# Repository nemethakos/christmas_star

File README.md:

# Christmas Star

Christmas Star is a Christmas ornament to be hanged onto a Christmas tree. 

It runs on a single AA Battery (Lithium, NiMh or Alkaline), has 31 APA102-2020 RGB LEDs driven by an ATMEGA 328P running on Arduino core. 
Gesture control by Avago APDS-9960 Gesture and Light sensor (sleep/wake up, next/previous effect).

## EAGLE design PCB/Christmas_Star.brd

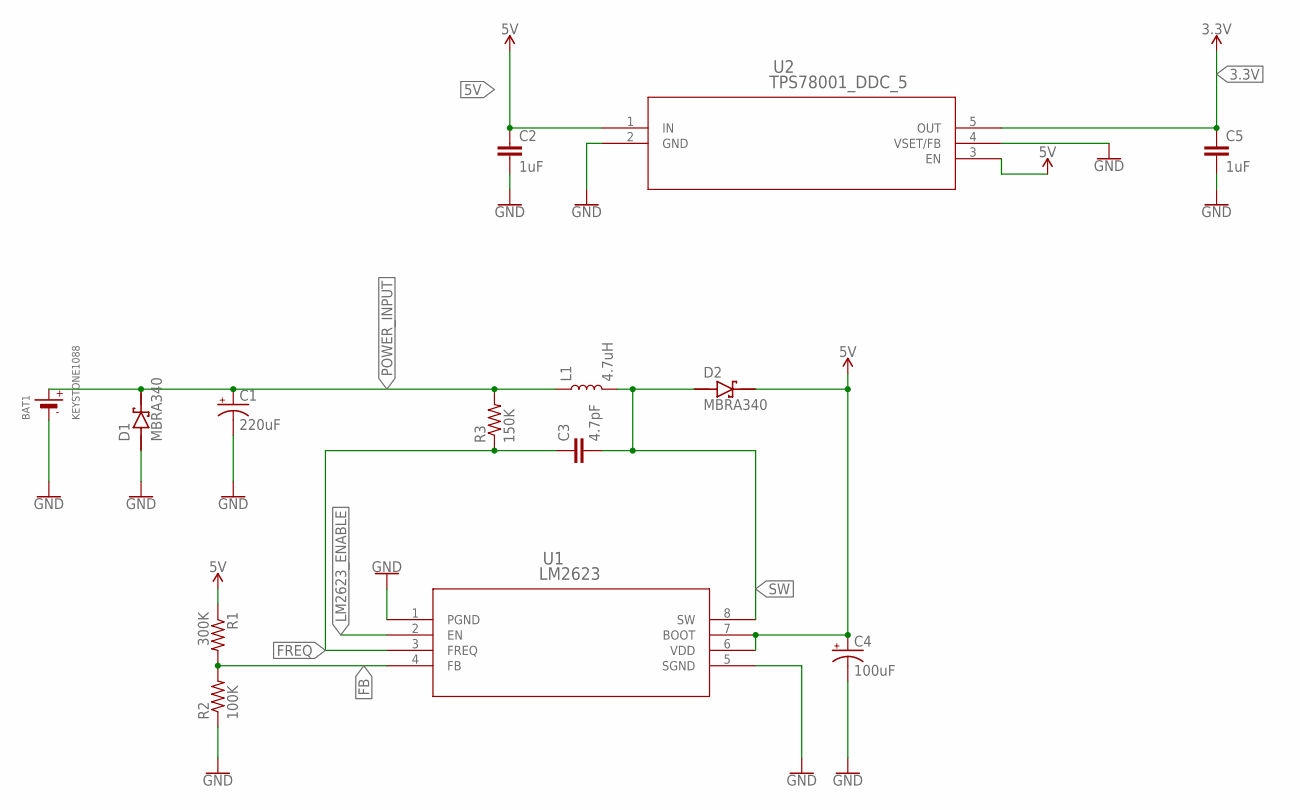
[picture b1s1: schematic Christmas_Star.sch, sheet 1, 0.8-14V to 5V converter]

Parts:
BAT1: KEYSTONE1088
C1: 220uF; EIA3528-KIT
C2, C5: 1uF; 0603-CAP
C3: 4.7pF; 0603-CAP
C4: 100uF; EIA3216-KIT
D1, D2: MBRA340; DIOM4427X270N
L1: 4.7uH; LTF5022
R1: 300K; 0603-RES
R2: 100K; 0603-RES
R3: 150K; 0603-RES
U1: LM2623; MUA08A
U2: TPS78001_DDC_5; DDC5

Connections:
3.3V: C5.1, U2.5 (OUT); also elsewhere on the board
5V: C2.1, C4.A (+), D2.C, R1.1, U1.6 (VDD), U1.7 (BOOT), U2.1 (IN), U2.3 (EN); also elsewhere on the board
FB: R1.2, R2.2, U1.4 (FB)
FREQ: C3.1, R3.1, U1.3 (FREQ)
GND: BAT1.-, C1.C (-), C2.2, C4.C (-), C5.2, D1.A, R2.1, U1.1 (PGND), U1.5 (SGND), U2.2 (GND), U2.4 (VSET/FB); also elsewhere on the board
LM2623_ENABLE: U1.2 (EN); also elsewhere on the board
POWER_INPUT: BAT1.+, C1.A (+), D1.C, L1.P$1 (1), R3.2; also elsewhere on the board
SW: C3.2, D2.A, L1.P$2 (2), U1.8 (SW)

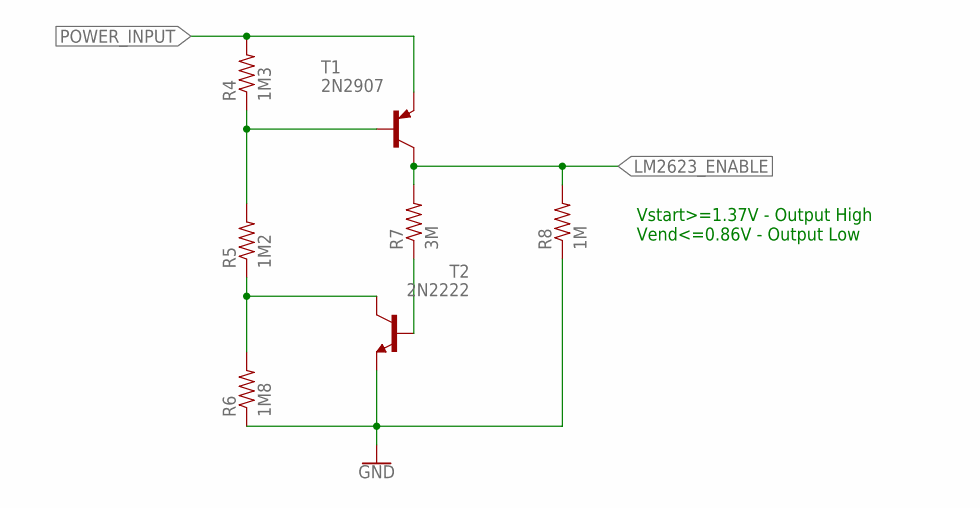
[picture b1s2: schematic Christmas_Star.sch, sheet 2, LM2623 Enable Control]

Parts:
R4: 1M3; 0603-RES
R5: 1M2; 0603-RES
R6: 1M8; 0603-RES
R7: 3M; 0603-RES
R8: 1M; 0603-RES
T1: 2N2907; SOT23-BEC
T2: 2N2222; SOT23-BEC

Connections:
GND: R6.1, R8.1, T2.E; also elsewhere on the board
LM2623_ENABLE: R7.2, R8.2, T1.C; also elsewhere on the board
unnamed: R4.1, R5.2, T1.B
unnamed: R5.1, R6.2, T2.C
unnamed: R7.1, T2.B
POWER_INPUT: R4.2, T1.E; also elsewhere on the board

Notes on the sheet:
Vstart>=1.37V - Output High Vend<=0.86V - Output Low

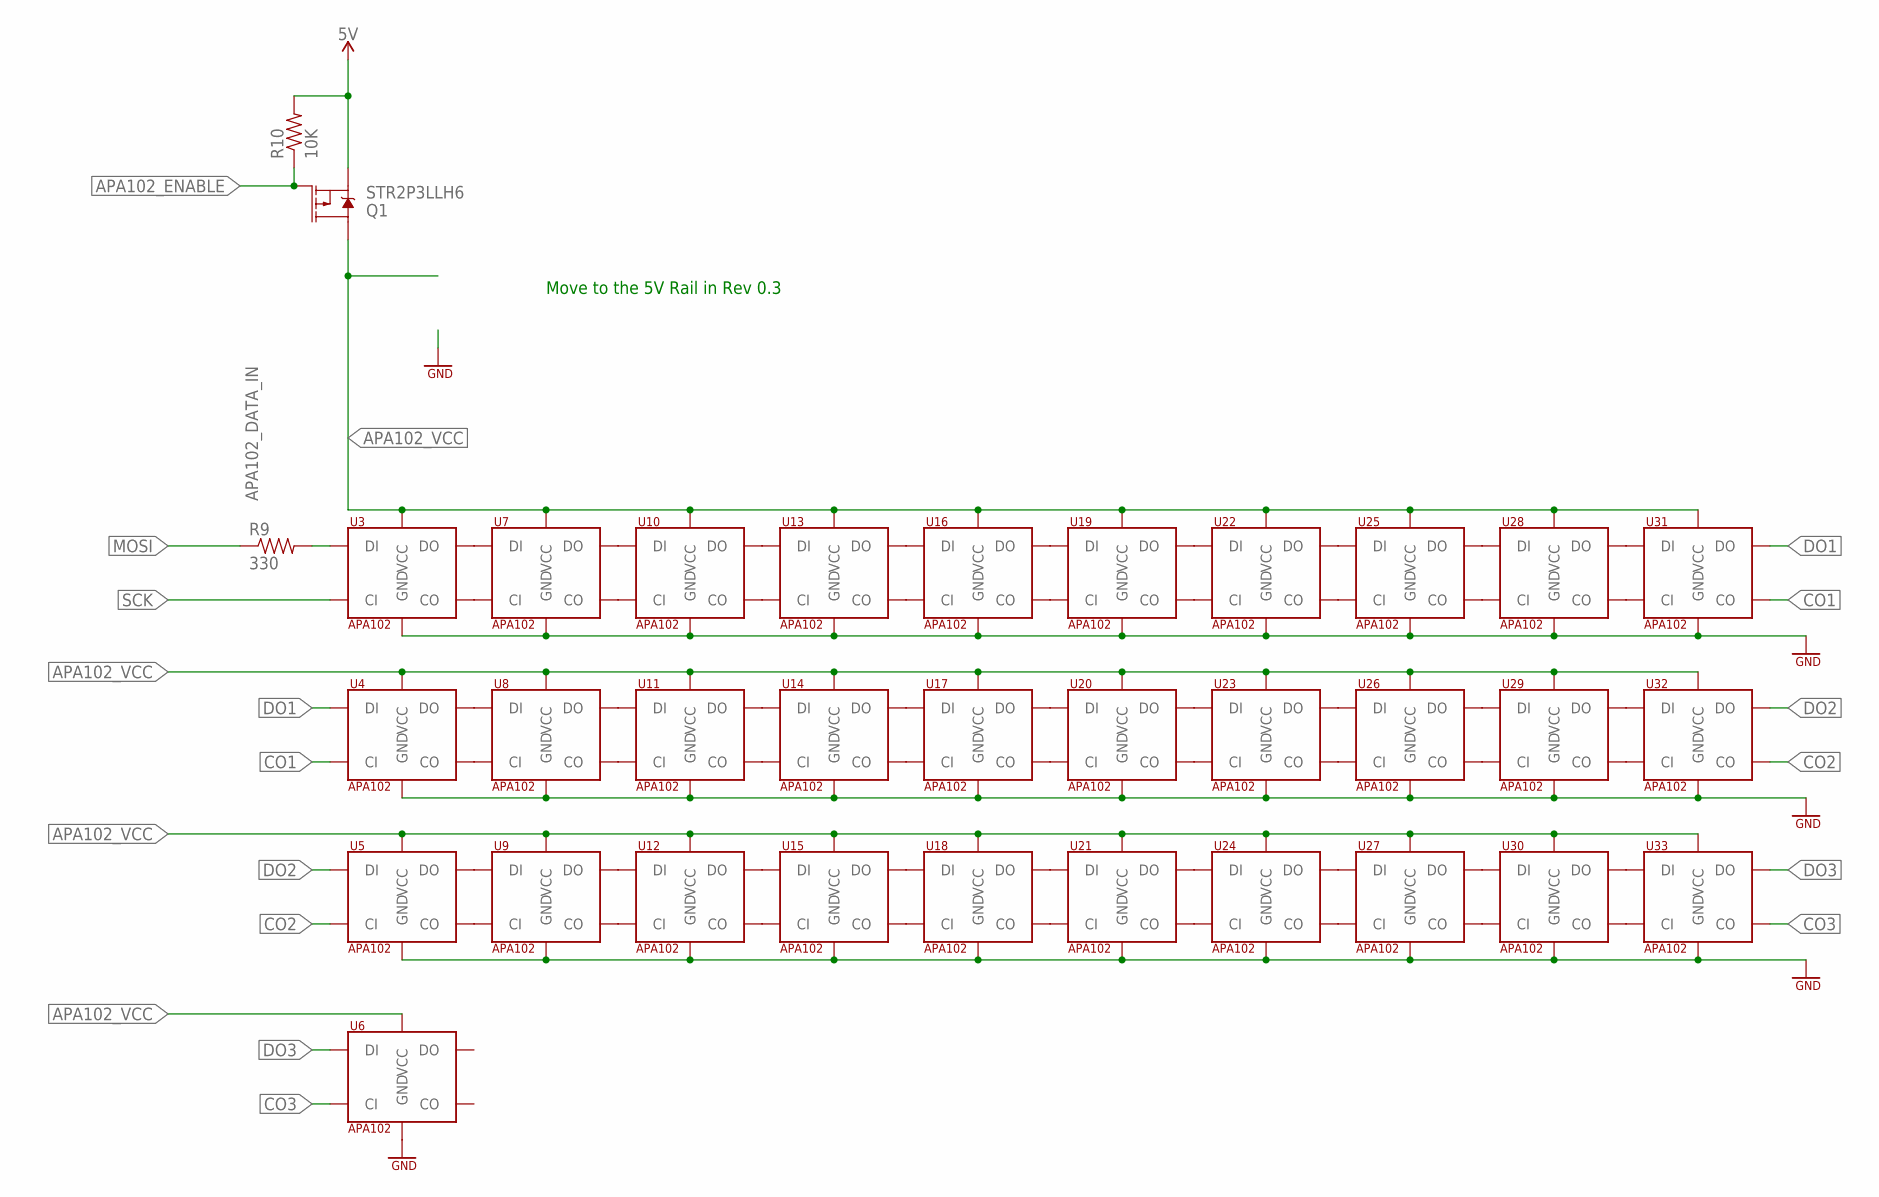
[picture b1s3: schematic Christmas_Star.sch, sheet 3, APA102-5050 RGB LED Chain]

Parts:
Q1: STR2P3LLH6; SOT23-3
R9: 330; 0603-RES
R10: 10K; 0603-RES
U3, U4, U5, U6, U7, U8, U9, U10, U11, U12, U13, U14, U15, U16, U17, U18, U19, U20, U21, U22, U23, U24, U25, U26, U27, U28, U29, U30, U31, U32, U33: APA102; APA102_2020

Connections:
5V: Q1.2 (S), R10.2; also elsewhere on the board
APA102_DATA_IN: R9.2, U3.D_IN (DI)
APA102_ENABLE: Q1.1 (G), R10.1; also elsewhere on the board
APA102_VCC: Q1.3 (D), U3.VCC, U4.VCC, U5.VCC, U6.VCC, U7.VCC, U8.VCC, U9.VCC, U10.VCC, U11.VCC, U12.VCC, U13.VCC, U14.VCC, U15.VCC, U16.VCC, U17.VCC, U18.VCC, U19.VCC, U20.VCC, U21.VCC, U22.VCC, U23.VCC, U24.VCC, U25.VCC, U26.VCC, U27.VCC, U28.VCC, U29.VCC, U30.VCC, U31.VCC, U32.VCC, U33.VCC
CO1: U4.C_IN (CI), U31.CL_OUT (CO)
CO2: U5.C_IN (CI), U32.CL_OUT (CO)
CO3: U6.C_IN (CI), U33.CL_OUT (CO)
DO1: U4.D_IN (DI), U31.D_OUT (DO)
DO2: U5.D_IN (DI), U32.D_OUT (DO)
DO3: U6.D_IN (DI), U33.D_OUT (DO)
GND: U3.GND, U4.GND, U5.GND, U6.GND, U7.GND, U8.GND, U9.GND, U10.GND, U11.GND, U12.GND, U13.GND, U14.GND, U15.GND, U16.GND, U17.GND, U18.GND, U19.GND, U20.GND, U21.GND, U22.GND, U23.GND, U24.GND, U25.GND, U26.GND, U27.GND, U28.GND, U29.GND, U30.GND, U31.GND, U32.GND, U33.GND; also elsewhere on the board
MOSI: R9.1; also elsewhere on the board
unnamed: U3.D_OUT (DO), U7.D_IN (DI)
unnamed: U3.CL_OUT (CO), U7.C_IN (CI)
unnamed: U7.D_OUT (DO), U10.D_IN (DI)
unnamed: U7.CL_OUT (CO), U10.C_IN (CI)
unnamed: U10.D_OUT (DO), U13.D_IN (DI)
unnamed: U10.CL_OUT (CO), U13.C_IN (CI)
unnamed: U13.D_OUT (DO), U16.D_IN (DI)
unnamed: U13.CL_OUT (CO), U16.C_IN (CI)
unnamed: U16.D_OUT (DO), U19.D_IN (DI)
unnamed: U16.CL_OUT (CO), U19.C_IN (CI)
unnamed: U19.D_OUT (DO), U22.D_IN (DI)
unnamed: U19.CL_OUT (CO), U22.C_IN (CI)
unnamed: U22.D_OUT (DO), U25.D_IN (DI)
unnamed: U22.CL_OUT (CO), U25.C_IN (CI)
unnamed: U25.D_OUT (DO), U28.D_IN (DI)
unnamed: U25.CL_OUT (CO), U28.C_IN (CI)
unnamed: U28.D_OUT (DO), U31.D_IN (DI)
unnamed: U28.CL_OUT (CO), U31.C_IN (CI)
unnamed: U4.D_OUT (DO), U8.D_IN (DI)
unnamed: U4.CL_OUT (CO), U8.C_IN (CI)
unnamed: U8.D_OUT (DO), U11.D_IN (DI)
unnamed: U8.CL_OUT (CO), U11.C_IN (CI)
unnamed: U11.D_OUT (DO), U14.D_IN (DI)
unnamed: U11.CL_OUT (CO), U14.C_IN (CI)
unnamed: U14.D_OUT (DO), U17.D_IN (DI)
unnamed: U14.CL_OUT (CO), U17.C_IN (CI)
unnamed: U17.D_OUT (DO), U20.D_IN (DI)
unnamed: U17.CL_OUT (CO), U20.C_IN (CI)
unnamed: U20.D_OUT (DO), U23.D_IN (DI)
unnamed: U20.CL_OUT (CO), U23.C_IN (CI)
unnamed: U23.D_OUT (DO), U26.D_IN (DI)
unnamed: U23.CL_OUT (CO), U26.C_IN (CI)
unnamed: U26.D_OUT (DO), U29.D_IN (DI)
unnamed: U26.CL_OUT (CO), U29.C_IN (CI)
unnamed: U29.D_OUT (DO), U32.D_IN (DI)
unnamed: U29.CL_OUT (CO), U32.C_IN (CI)
unnamed: U5.D_OUT (DO), U9.D_IN (DI)
unnamed: U5.CL_OUT (CO), U9.C_IN (CI)
unnamed: U9.D_OUT (DO), U12.D_IN (DI)
unnamed: U9.CL_OUT (CO), U12.C_IN (CI)
unnamed: U12.D_OUT (DO), U15.D_IN (DI)
unnamed: U12.CL_OUT (CO), U15.C_IN (CI)
unnamed: U15.D_OUT (DO), U18.D_IN (DI)
unnamed: U15.CL_OUT (CO), U18.C_IN (CI)
unnamed: U18.D_OUT (DO), U21.D_IN (DI)
unnamed: U18.CL_OUT (CO), U21.C_IN (CI)
unnamed: U21.D_OUT (DO), U24.D_IN (DI)
unnamed: U21.CL_OUT (CO), U24.C_IN (CI)
unnamed: U24.D_OUT (DO), U27.D_IN (DI)
unnamed: U24.CL_OUT (CO), U27.C_IN (CI)
unnamed: U27.D_OUT (DO), U30.D_IN (DI)
unnamed: U27.CL_OUT (CO), U30.C_IN (CI)
unnamed: U30.D_OUT (DO), U33.D_IN (DI)
unnamed: U30.CL_OUT (CO), U33.C_IN (CI)
SCK: U3.C_IN (CI); also elsewhere on the board

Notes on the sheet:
Move to the 5V Rail in Rev 0.3

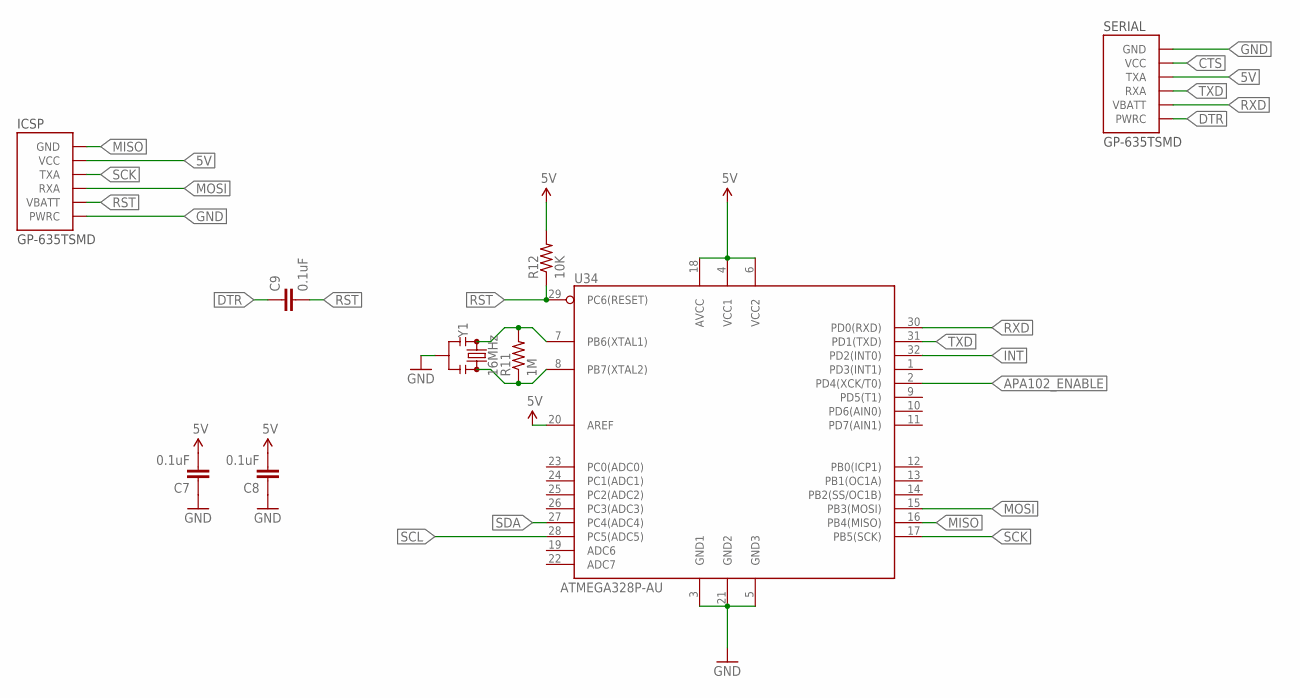
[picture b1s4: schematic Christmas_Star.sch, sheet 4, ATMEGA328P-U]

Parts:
C7, C8, C9: 0.1uF; 0603-CAP
ICSP: GP-635TSMD; GP-635T
R11: 1M; 0603-RES
R12: 10K; 0603-RES
SERIAL: GP-635TSMD; GP-635T
U34: ATMEGA328P-AU; TQFP32
Y1: 16MHz; RESONATOR-SMD-3.2X1.3

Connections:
5V: C7.2, C8.2, ICSP.2 (VCC), R12.2, SERIAL.3 (TXA), U34.4 (VCC1), U34.6 (VCC2), U34.18 (AVCC), U34.20 (AREF); also elsewhere on the board
APA102_ENABLE: U34.2 (PD4(XCK/T0)); also elsewhere on the board
CTS: SERIAL.2 (VCC)
DTR: C9.1, SERIAL.6 (PWRC)
GND: C7.1, C8.1, ICSP.6 (PWRC), SERIAL.1 (GND), U34.3 (GND1), U34.5 (GND3), U34.21 (GND2), Y1.2; also elsewhere on the board
INT: U34.32 (PD2(INT0)); also elsewhere on the board
MISO: ICSP.1 (GND), U34.16 (PB4(MISO))
MOSI: ICSP.4 (RXA), U34.15 (PB3(MOSI)); also elsewhere on the board
unnamed: R11.2, U34.7 (PB6(XTAL1)), Y1.1
unnamed: R11.1, U34.8 (PB7(XTAL2)), Y1.3
RST: C9.2, ICSP.5 (VBATT), R12.1, U34.29 (PC6(RESET))
RXD: SERIAL.5 (VBATT), U34.30 (PD0(RXD))
SCK: ICSP.3 (TXA), U34.17 (PB5(SCK)); also elsewhere on the board
SCL: U34.28 (PC5(ADC5)); also elsewhere on the board
SDA: U34.27 (PC4(ADC4)); also elsewhere on the board
TXD: SERIAL.4 (RXA), U34.31 (PD1(TXD))

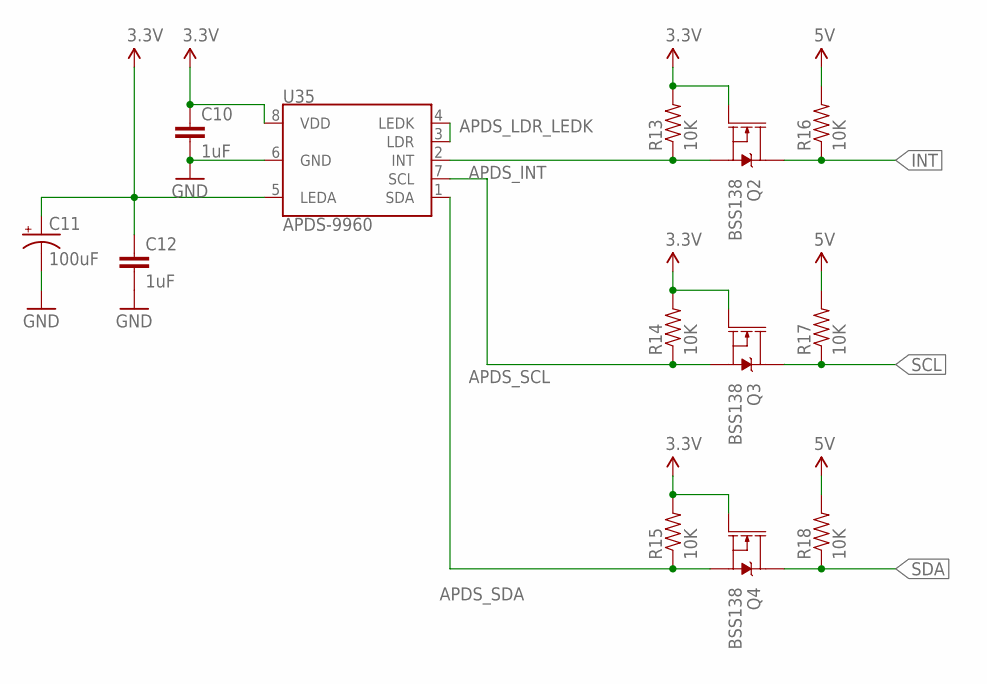
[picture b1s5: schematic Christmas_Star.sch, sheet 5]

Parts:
C10, C12: 1uF; 0603-CAP
C11: 100uF; EIA3216-KIT
Q2, Q3, Q4: BSS138; SOT23-3
R13, R14, R15, R16, R17, R18: 10K; 0603-RES
U35: APDS-9960

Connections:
3.3V: C10.1, C11.A (+), C12.1, Q2.1 (G), Q3.1 (G), Q4.1 (G), R13.2, R14.2, R15.2, U35.5 (LEDA), U35.8 (VDD); also elsewhere on the board
5V: R16.2, R17.2, R18.2; also elsewhere on the board
APDS_INT: Q2.2 (S), R13.1, U35.2 (INT)
APDS_LDR_LEDK: U35.3 (LDR), U35.4 (LEDK)
APDS_SCL: Q3.2 (S), R14.1, U35.7 (SCL)
APDS_SDA: Q4.2 (S), R15.1, U35.1 (SDA)
GND: C10.2, C11.C (-), C12.2, U35.6 (GND); also elsewhere on the board
INT: Q2.3 (D), R16.1; also elsewhere on the board
SCL: Q3.3 (D), R17.1; also elsewhere on the board
SDA: Q4.3 (D), R18.1; also elsewhere on the board

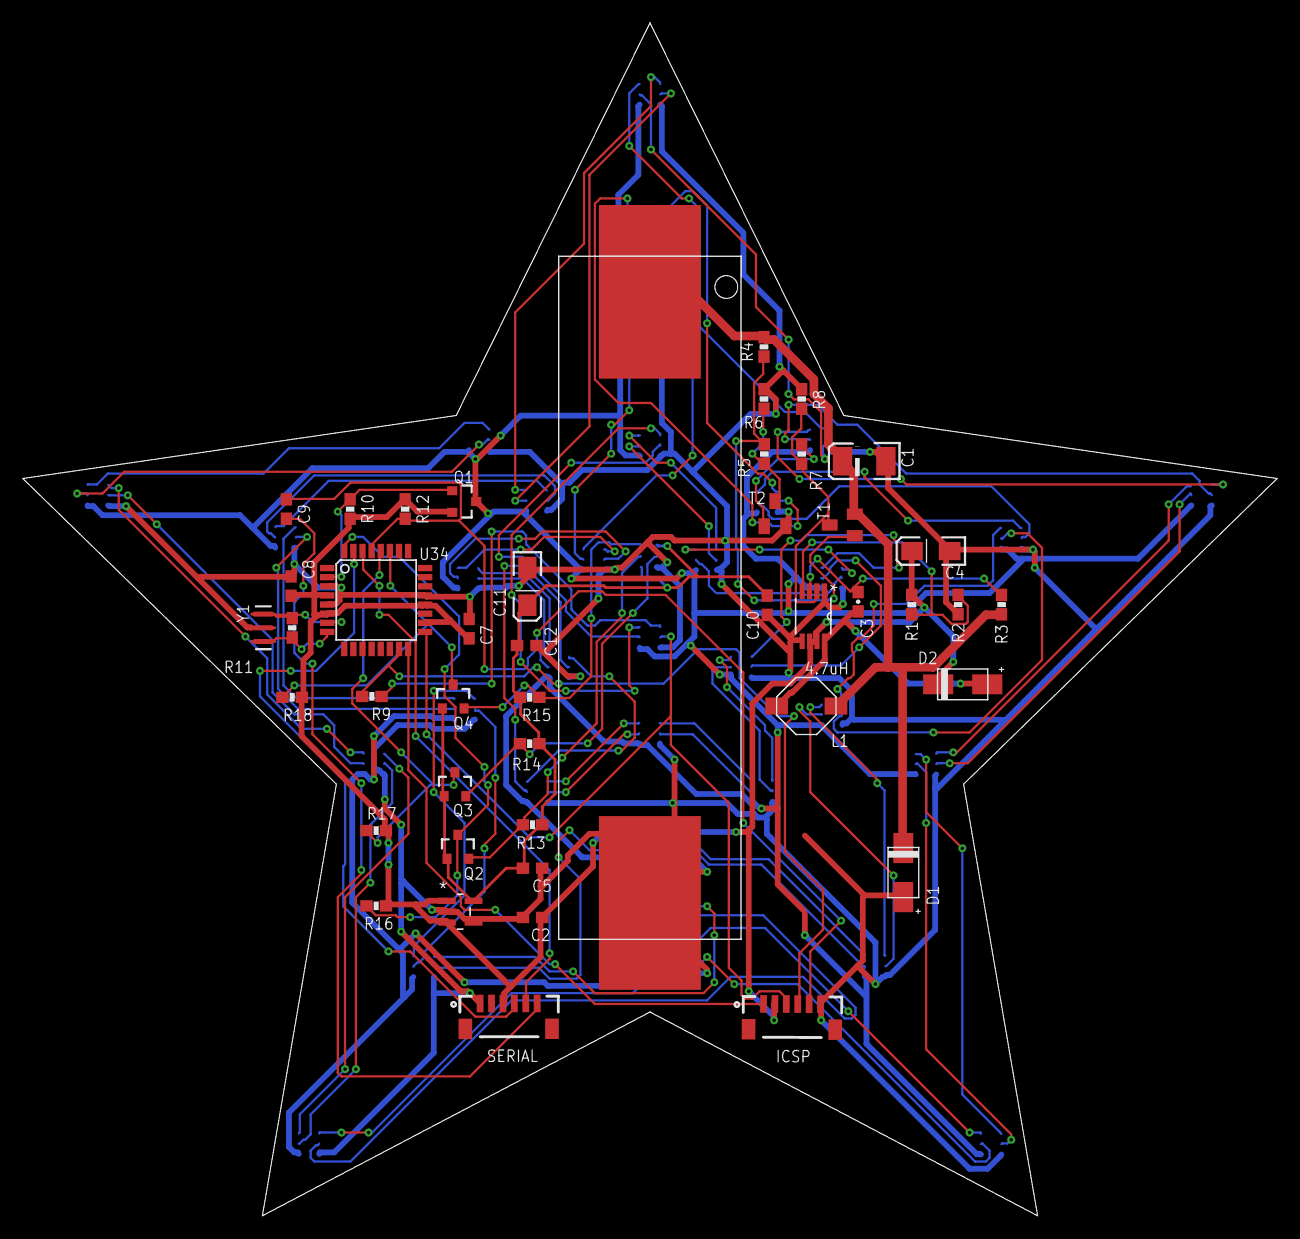
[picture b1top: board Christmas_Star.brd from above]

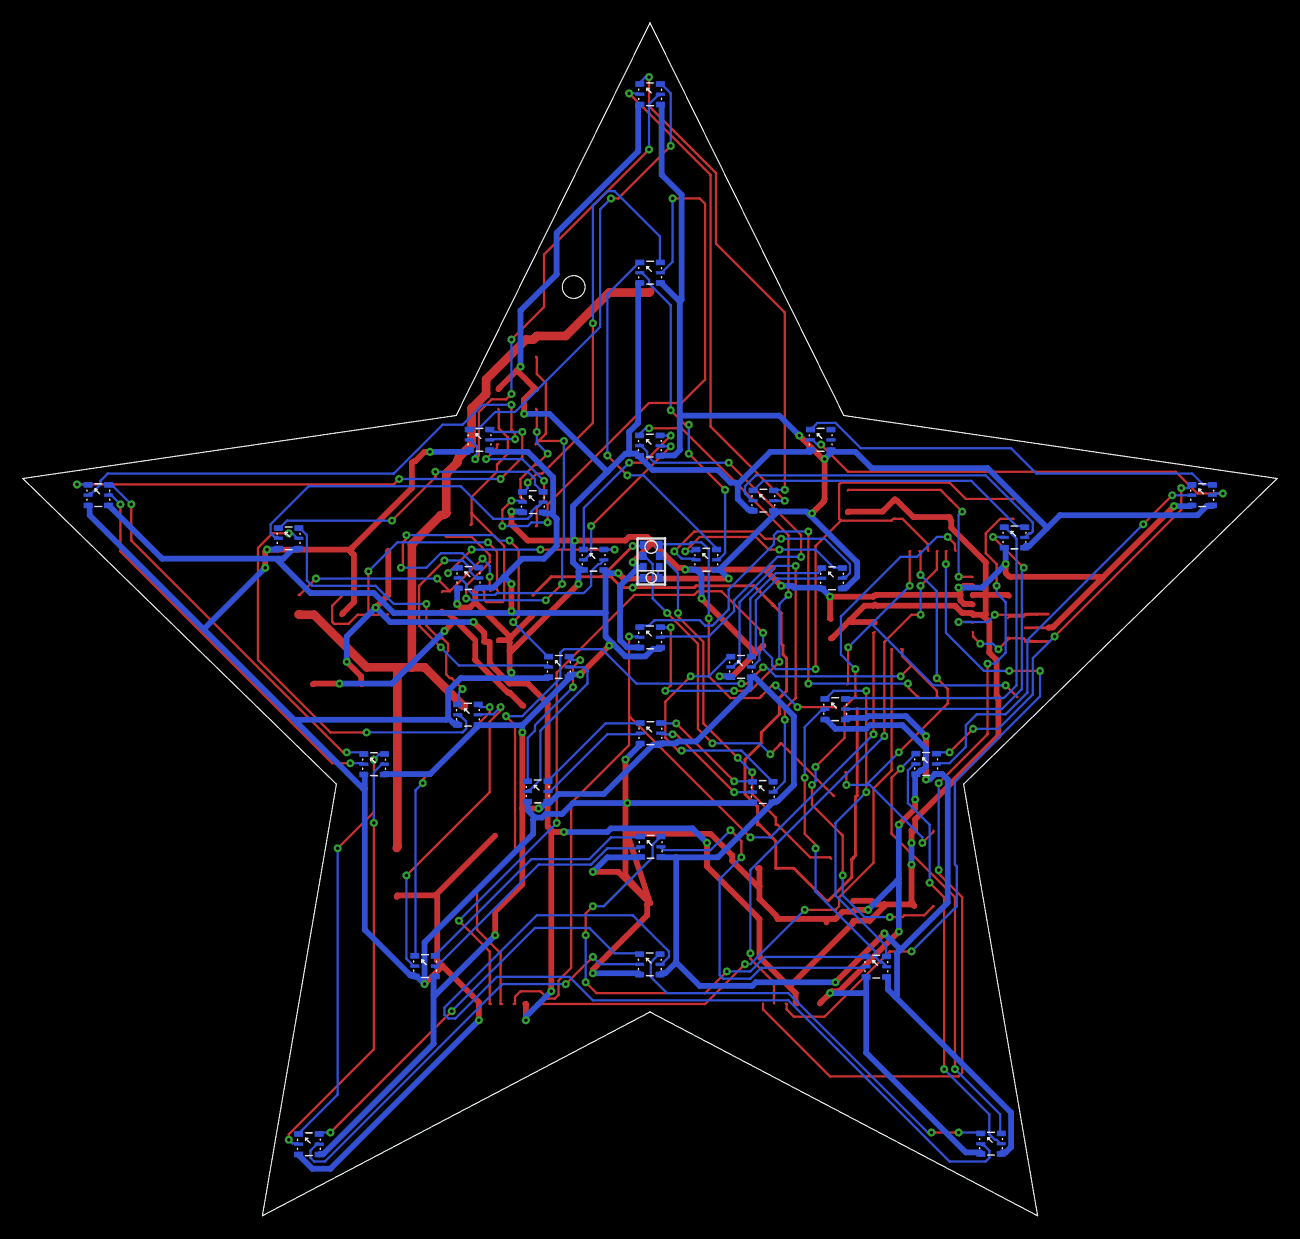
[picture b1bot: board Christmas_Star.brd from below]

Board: 2 copper layers, 110.0 x 104.6 mm, 77 parts (32 on the bottom side), 90 nets.

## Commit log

2018-07-07 Christmas Star initial
2018-07-08 Photo added
2018-07-08 Readme added
2018-07-08 Title changed
2018-07-08 Eagle files for PCB Xara+Inkscape files for board layout BOM Gerber files for PCB manufacturing
2018-07-08 Eagle+BOM+Gerbers Images of the schematics
2018-07-09 license added

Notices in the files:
parts and their libraries:
SparkFun-Capacitors: Licensing: Creative Commons ShareAlike 4.0 International - https://creativecommons.org/licenses/by-sa/4.0
